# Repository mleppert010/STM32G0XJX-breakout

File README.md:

Breakout board with decoupling for SON-8 STM32G0/C0

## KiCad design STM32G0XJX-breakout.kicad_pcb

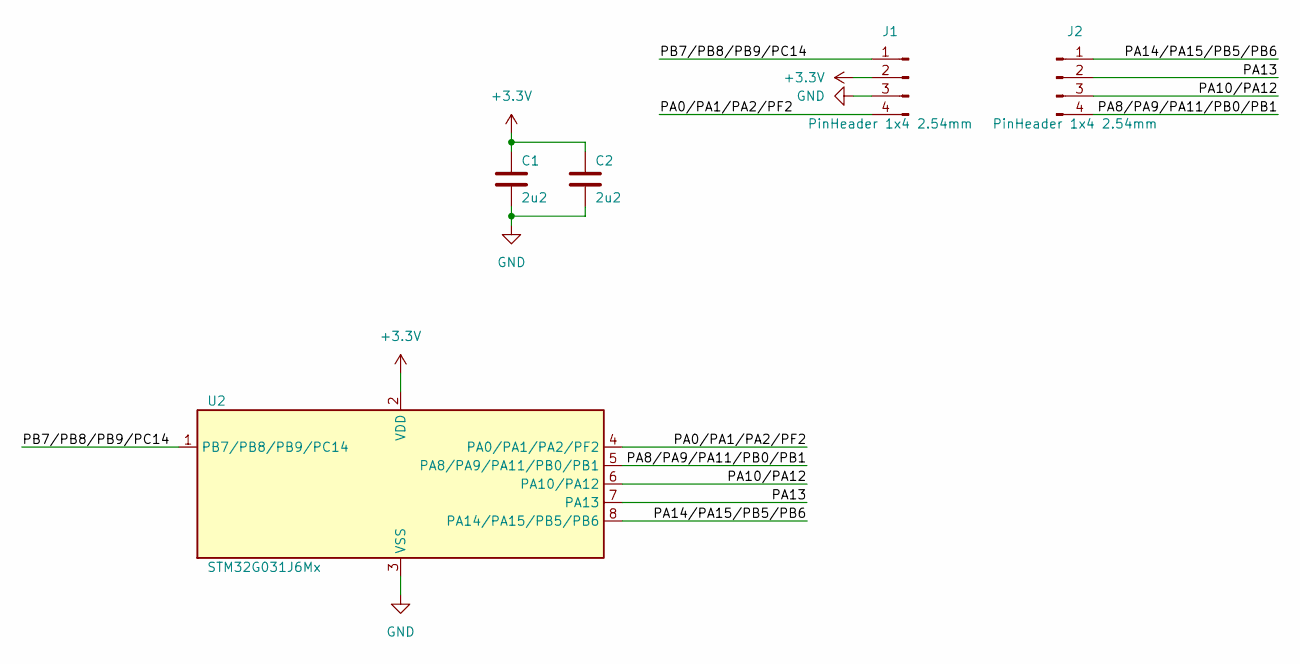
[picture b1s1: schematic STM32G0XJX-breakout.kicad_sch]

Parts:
C1, C2: 2u2; C_0603_1608Metric
J1, J2: PinHeader 1x4 2.54mm; SAMTEC_TS-104-T-AA
U2: STM32G031J6Mx; JEITA_SOIC-8_3.9x4.9mm_P1.27mm

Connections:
+3.3V: C1.1, C2.1, J1.2, U2.2 (VDD)
/PA0/PA1/PA2/PF2: J1.4, U2.4 (PA0/PA1/PA2/PF2)
/PA8/PA9/PA11/PB0/PB1: J2.4, U2.5 (PA8/PA9/PA11/PB0/PB1)
/PA10/PA12: J2.3, U2.6 (PA10/PA12)
/PA13: J2.2, U2.7 (PA13)
/PA14/PA15/PB5/PB6: J2.1, U2.8 (PA14/PA15/PB5/PB6)
/PB7/PB8/PB9/PC14: J1.1, U2.1 (PB7/PB8/PB9/PC14)
GND: C1.2, C2.2, J1.3, U2.3 (VSS)

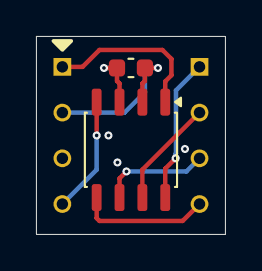
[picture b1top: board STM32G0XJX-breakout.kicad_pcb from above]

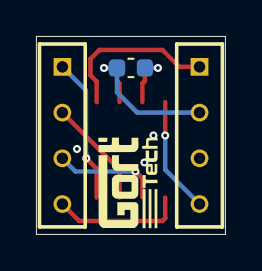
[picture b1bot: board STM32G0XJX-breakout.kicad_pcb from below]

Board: 4 copper layers, 10.5 x 11.0 mm, 5 parts (3 on the bottom side), 8 nets.

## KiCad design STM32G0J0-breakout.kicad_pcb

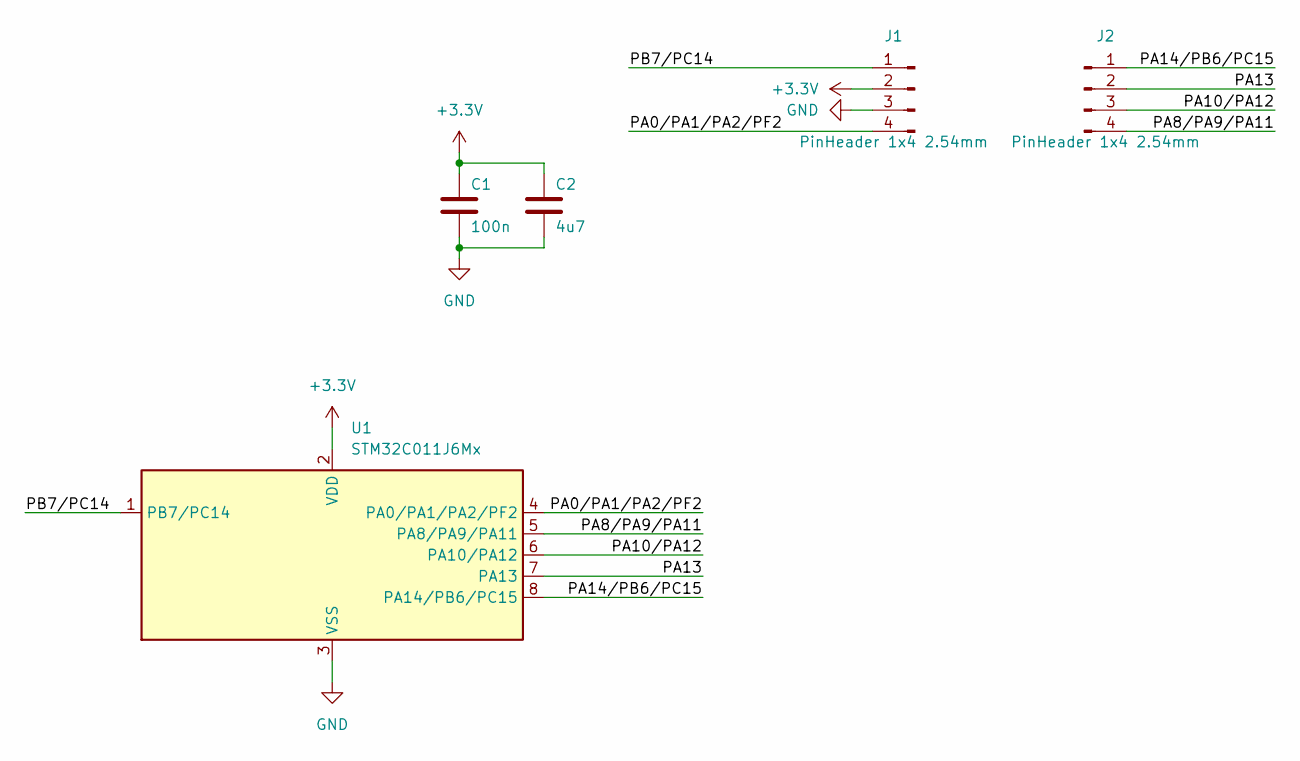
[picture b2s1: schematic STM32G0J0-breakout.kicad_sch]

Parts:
C1: 100n; C_0805_2012Metric
C2: 4u7; C_0805_2012Metric
J1, J2: PinHeader 1x4 2.54mm; SAMTEC_TS-104-T-AA
U1: STM32C011J6Mx; SOIC-8_3.9x4.9mm_P1.27mm

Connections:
+3.3V: C1.1, C2.1, J1.2, U1.2 (VDD)
/PA0/PA1/PA2/PF2: J1.4, U1.4 (PA0/PA1/PA2/PF2)
/PA8/PA9/PA11: J2.4, U1.5 (PA8/PA9/PA11)
/PA10/PA12: J2.3, U1.6 (PA10/PA12)
/PA13: J2.2, U1.7 (PA13)
/PA14/PB6/PC15: J2.1, U1.8 (PA14/PB6/PC15)
/PB7/PC14: J1.1, U1.1 (PB7/PC14)
GND: C1.2, C2.2, J1.3, U1.3 (VSS)

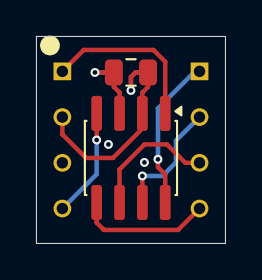
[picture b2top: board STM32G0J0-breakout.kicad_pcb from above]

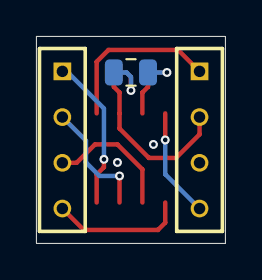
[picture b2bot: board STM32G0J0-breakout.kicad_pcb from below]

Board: 4 copper layers, 10.5 x 11.5 mm, 5 parts (3 on the bottom side), 8 nets.
